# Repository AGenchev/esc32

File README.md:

# code taken from esc32, reworked to compile with GCC/freeware toolchain

I modified this and reformed the project... The goal - to compile with FOSS tools completely and to contain all source.
I put in a PCB hardware design to test it.
I probably have introduced new bugs.

First "problem": When I compiled with GCC, I got less CPU free time than the binary from esc32. Thus the control loop was closer to take 100% of the CPU time.
I considered this dangerous, because the control loop is timer-driven, e.t. in IRQ. Resolution path taken: to rewrite the control loop in integer. Most of it's done, RPM calculation is still in floating point though.

The ESC code is in <a href=https://github.com/AGenchev/esc32/tree/gelemod02/onboard>"onboard"</a> directory. <br/>
The <a href=https://github.com/AGenchev/esc32/tree/gelemod02/ground>"ground"</a> directory contains the utility which tunes the rpm PID and the current limiter PID. It does not work yet with my hardware as I have not modified it. Actually I use the ESC with current limiter turned off.

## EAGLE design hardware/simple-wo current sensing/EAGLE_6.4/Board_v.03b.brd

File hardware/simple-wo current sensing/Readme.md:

This was designed for a friend who wanted simplest design. Current sensing amplifier and shunt were removed.

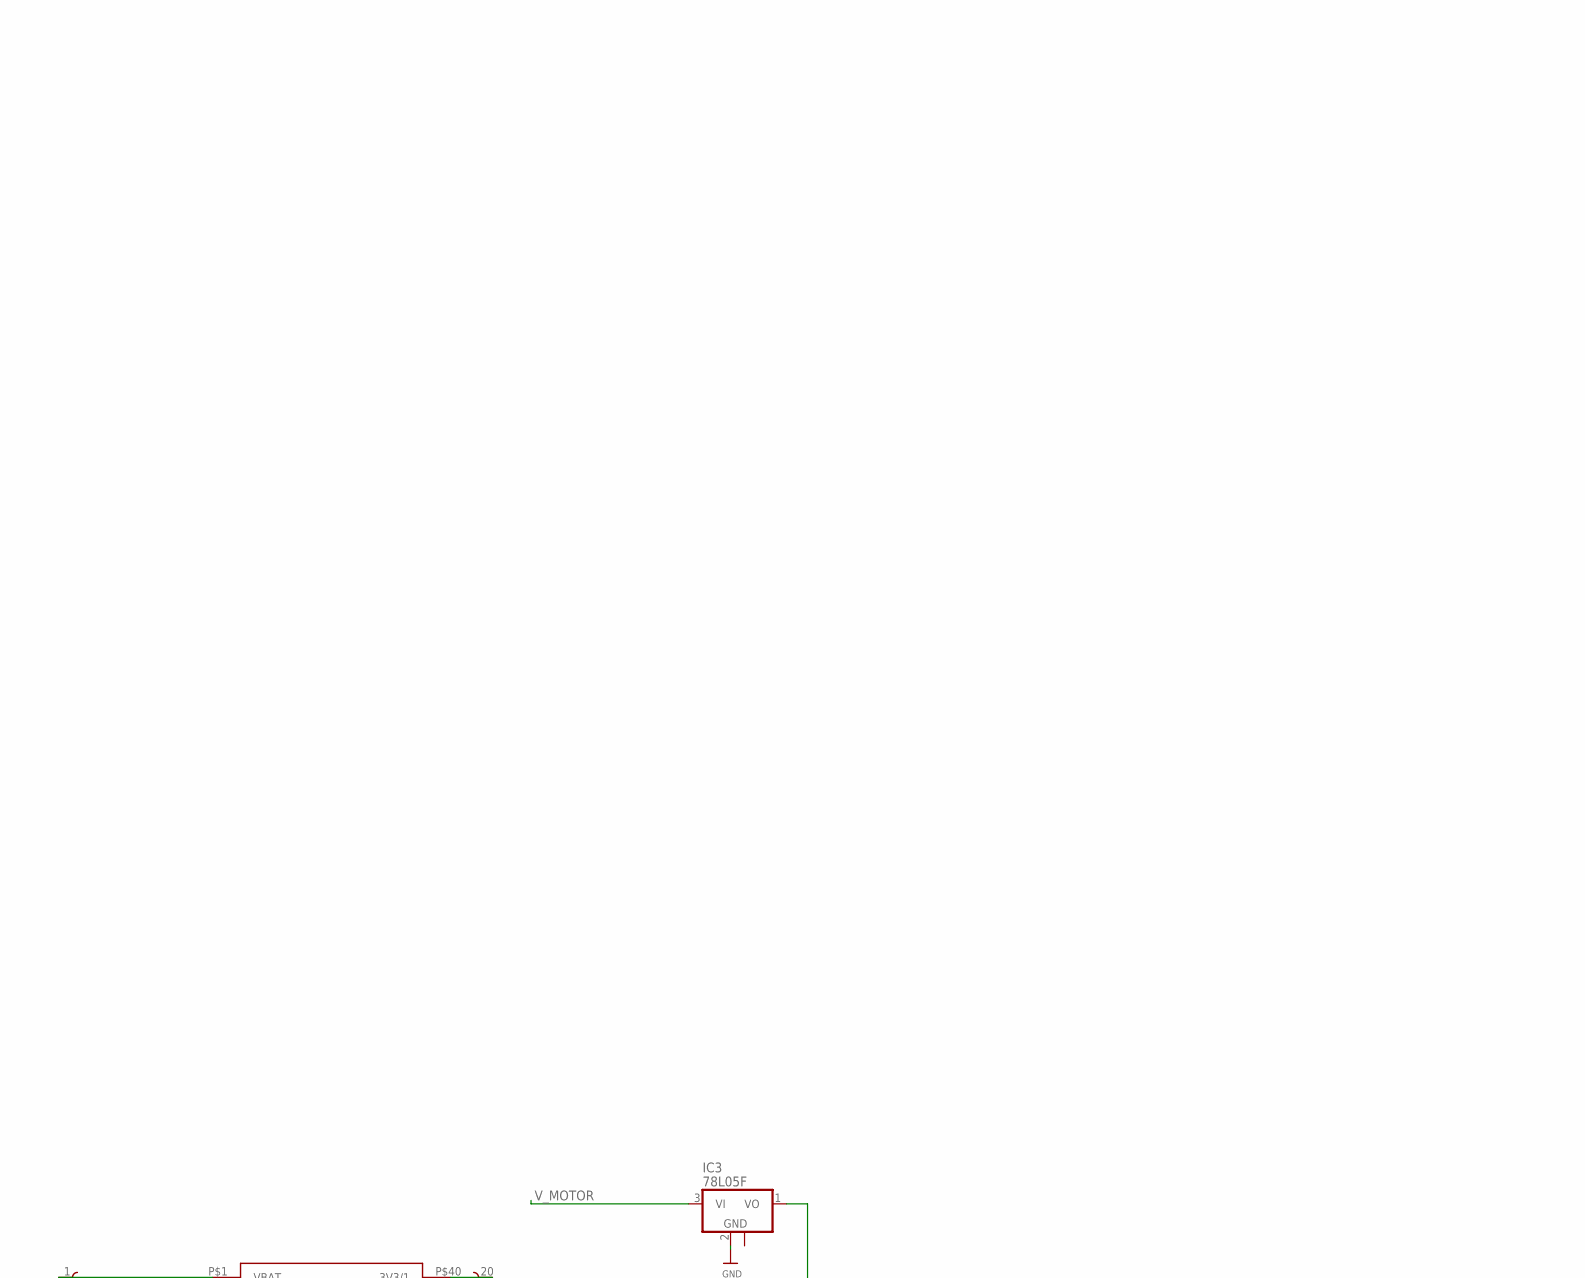
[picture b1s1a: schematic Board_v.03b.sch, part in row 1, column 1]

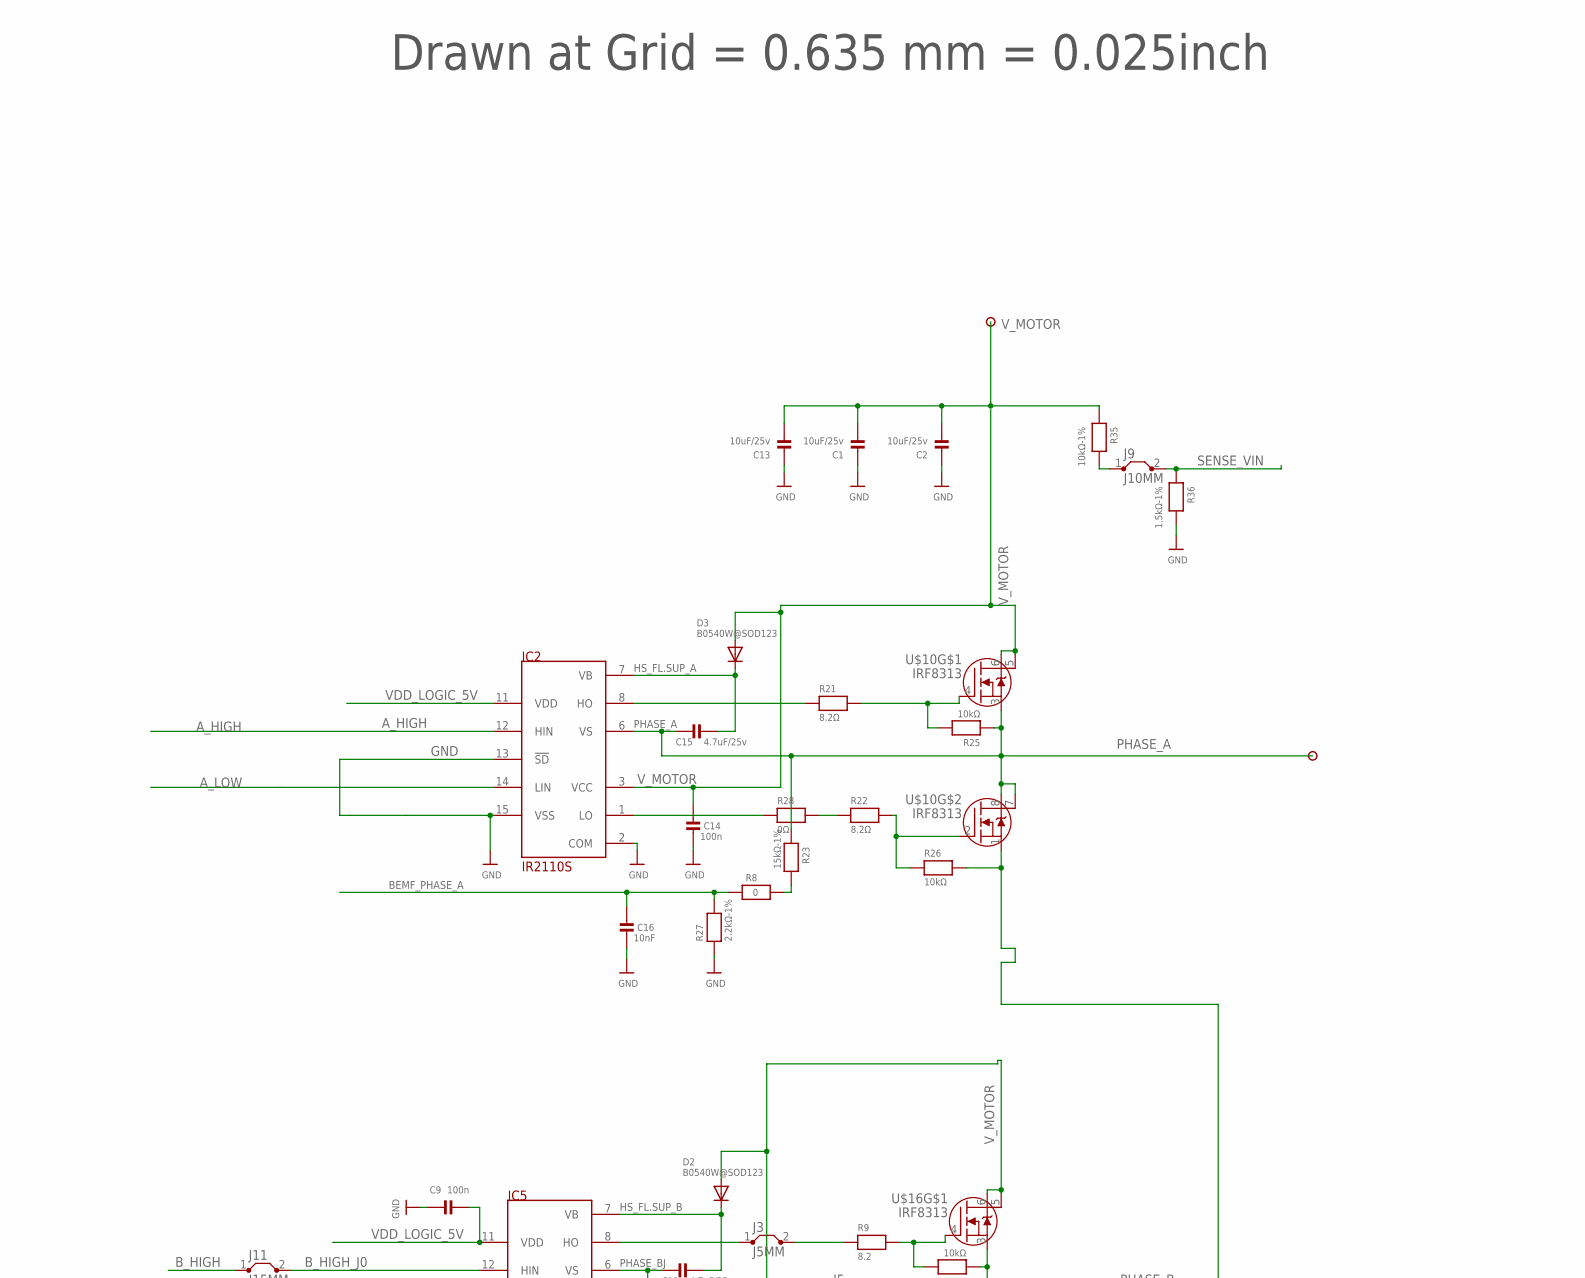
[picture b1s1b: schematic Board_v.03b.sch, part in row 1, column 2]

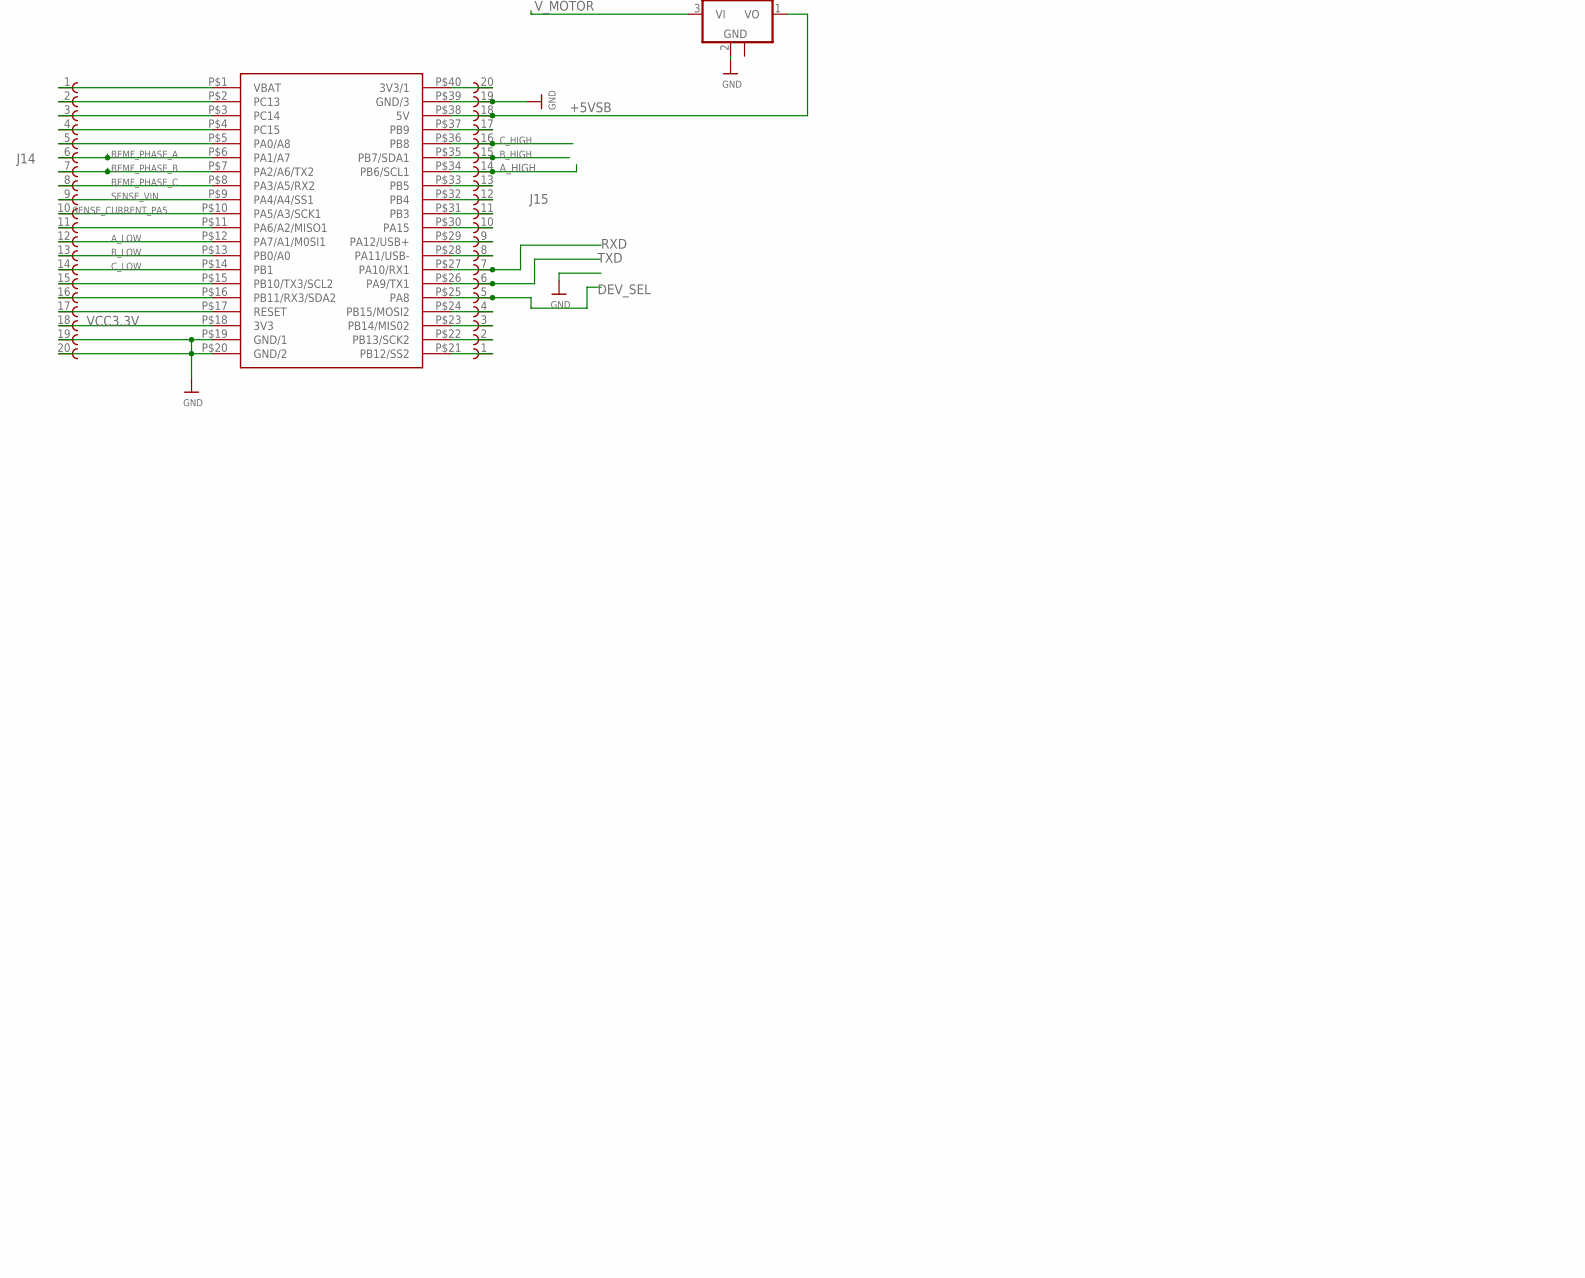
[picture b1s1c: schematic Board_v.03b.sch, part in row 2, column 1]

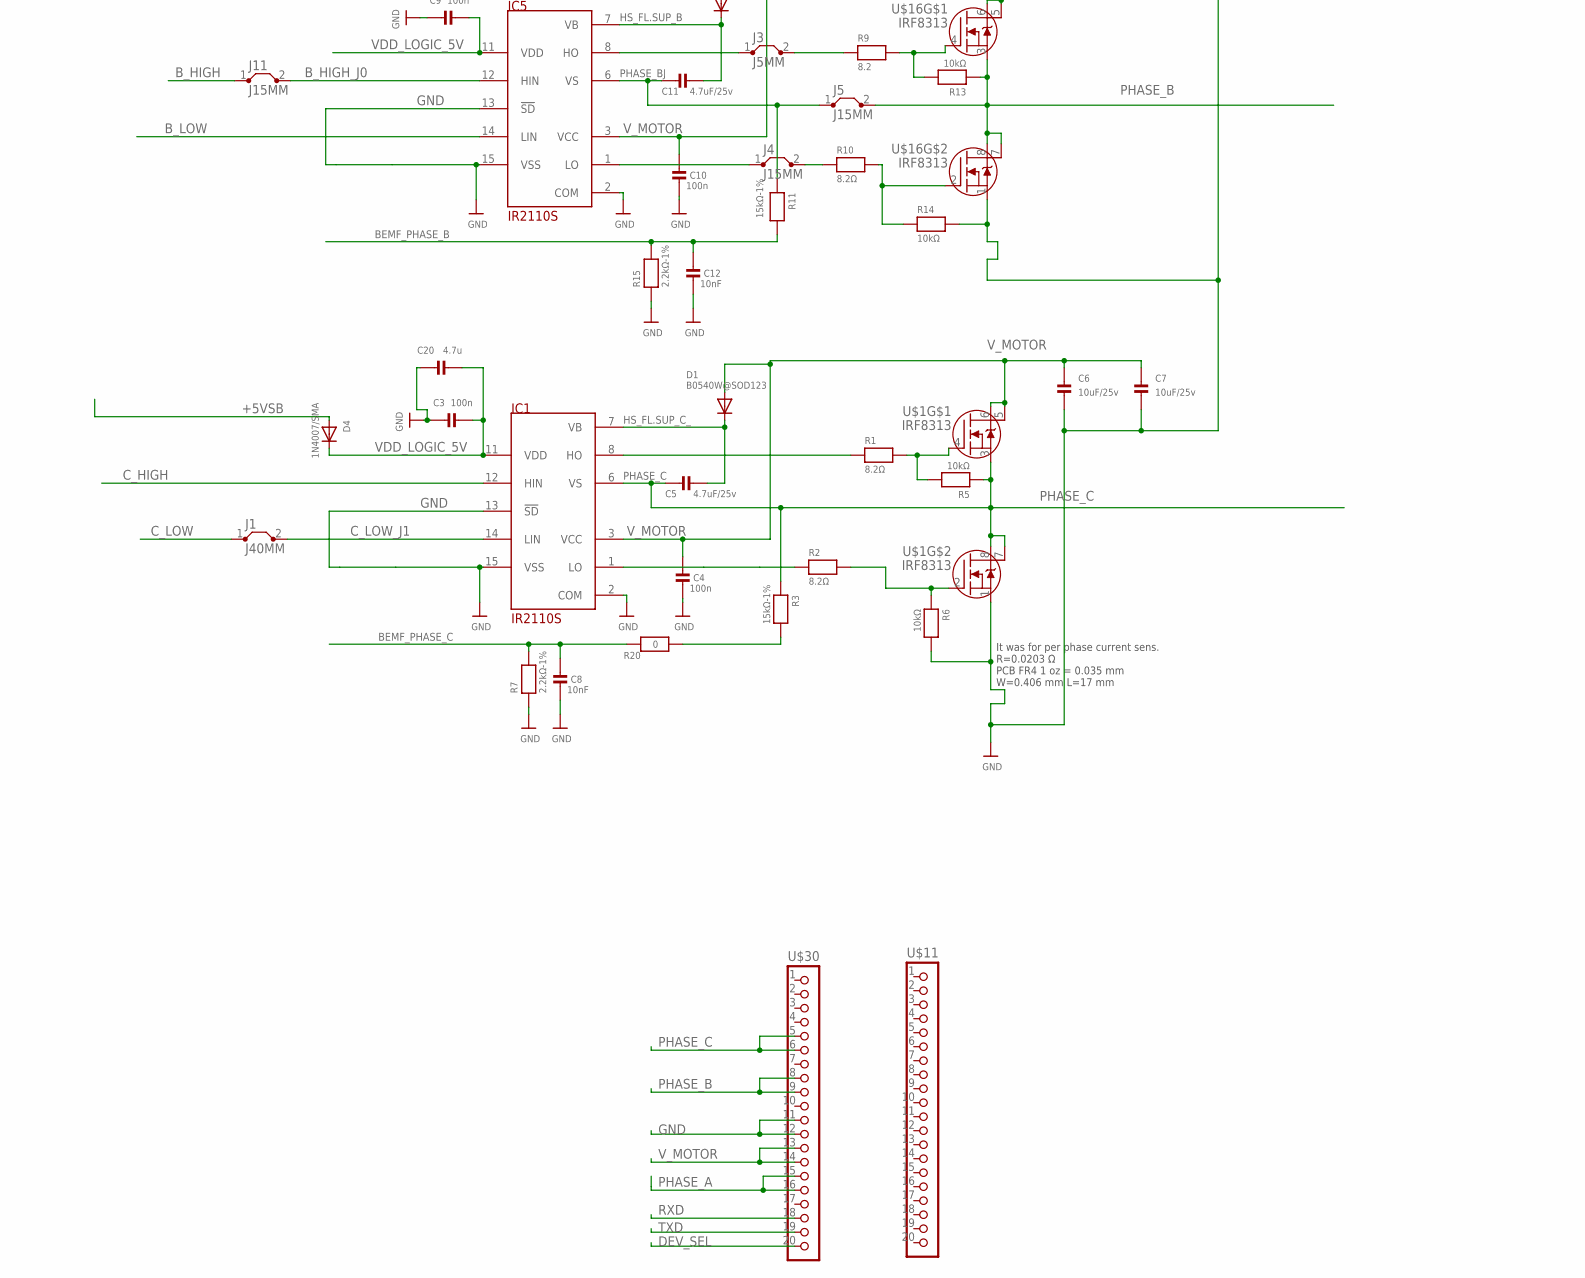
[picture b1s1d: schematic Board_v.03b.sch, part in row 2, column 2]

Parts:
C1, C2, C6, C7, C13: 10uF/25v; _0805MP
C3: 100n; _0805MP
C4, C9, C10, C14: 100n; _0603MP
C5, C11, C15: 4.7uF/25v; _0805MP
C8, C12, C16: 10nF; _0805MP
C20: 4.7u; _0805MP
D1, D2, D3: B0540W@SOD123; SOD-123
D4: 1N4007/SMA; SMADIODE
IC1, IC2, IC5: IR2110S; SO-16DW
IC3: 78L05F; SOT89
J1: J40MM
J3: J5MM; 05
J4, J5, J11: J15MM; 15
J9: J10MM; 10
J14, J15: 61002013321; CON-20PIN-SMD-MANUALLY-BENT-FROM-NON-SMD
PHASE_C: PHASE_C; PAD
R1, R2, R10, R21, R22: 8.2Ω; _0805MP
R3, R11, R23: 15kΩ-1%; _0805MP
R5, R6, R13, R14, R25, R26: 10kΩ; _0805MP
R7, R15, R27: 2.2kΩ-1%; _0805MP
R8, R20: 0; _0805MP
R9: 8.2; _0805MP
R28: 0Ω; _0805MP
R35: 10kΩ-1%; _0805MP
R36: 1.5kΩ-1%; _0805MP
U$1, U$10, U$16: IRF8313; SO08
U$11, U$30: CON_HEADER_1X20; M1X20_SMD_2.54MM/0.1"_LONGTRACKS
U$36: BLUEPILL; 40-DIP-BLUE-PIL
V_MOTOR: V_MOTOR; PAD

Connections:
+5VSB: D4.A, IC3.1 (VO), J15.18, U$36.P$38 (5V)
A_HIGH: IC2.12 (HIN), J15.14, U$36.P$34 (PB6/SCL1)
A_LOW: IC2.14 (LIN), J14.12, U$36.P$12 (PA7/A1/M0SI1)
BEMF_PHASE_A: C16.2, J14.6, R8.1, R27.2, U$36.P$6 (PA1/A7)
BEMF_PHASE_B: C12.2, J14.7, R11.2, R15.2, U$36.P$7 (PA2/A6/TX2)
BEMF_PHASE_C: C8.2, J14.8, R7.2, R20.2, U$36.P$8 (PA3/A5/RX2)
B_HIGH: J11.1, J15.15, U$36.P$35 (PB7/SDA1)
B_HIGH_J0: IC5.12 (HIN), J11.2
B_LOW: IC5.14 (LIN), J14.13, U$36.P$13 (PB0/A0)
C_HIGH: IC1.12 (HIN), J15.16, U$36.P$36 (PB8)
C_LOW: J1.1, J14.14, U$36.P$14 (PB1)
C_LOW_J1: IC1.14 (LIN), J1.2
DEV_SEL: J15.5, U$30.20, U$36.P$25 (PA8)
GND: C1.1, C2.1, C3.1, C4.1, C6.2, C7.2, C8.1, C9.1, C10.1, C12.1, C13.1, C14.1, C16.1, C20.1, IC1.2 (COM), IC1.13 (!SD), IC1.15 (VSS), IC2.2 (COM), IC2.13 (!SD), IC2.15 (VSS), IC3.2 (GND), IC5.2 (COM), IC5.13 (!SD), IC5.15 (VSS), J14.19, J14.20, J15.19, R6.2, R7.1, R14.2, R15.1, R26.2, R27.1, R36.2, U$1.1 (S), U$10.1 (S), U$16.1 (S), U$30.11, U$30.12, U$36.P$19 (GND/1), U$36.P$20 (GND/2), U$36.P$39 (GND/3)
HS_FL.SUP_A: C15.1, D3.C, IC2.7 (VB)
HS_FL.SUP_B: C11.1, D2.C, IC5.7 (VB)
HS_FL.SUP_C_: C5.1, D1.C, IC1.7 (VB)
unnamed: R1.2, R5.2, U$1.4 (G)
unnamed: J3.2, R9.1
unnamed: R2.2, R6.1, U$1.2 (G)
unnamed: IC1.8 (HO), R1.1
unnamed: IC1.1 (LO), R2.1
unnamed: R8.2, R23.2
unnamed: R3.2, R20.1
unnamed: R9.2, R13.2, U$16.4 (G)
unnamed: IC5.8 (HO), J3.1
unnamed: R10.2, R14.1, U$16.2 (G)
unnamed: J4.2, R10.1
unnamed: IC5.1 (LO), J4.1
unnamed: R21.2, R25.2, U$10.4 (G)
unnamed: R22.2, R26.1, U$10.2 (G)
unnamed: IC2.8 (HO), R21.1
unnamed: R22.1, R28.2
unnamed: IC2.1 (LO), R28.1
unnamed: J14.5, U$36.P$5 (PA0/A8)
unnamed: J9.1, R35.2
unnamed: J14.1, U$36.P$1 (VBAT)
unnamed: J14.2, U$36.P$2 (PC13)
unnamed: J14.3, U$36.P$3 (PC14)
unnamed: J14.4, U$36.P$4 (PC15)
unnamed: J14.11, U$36.P$11 (PA6/A2/MISO1)
unnamed: J14.15, U$36.P$15 (PB10/TX3/SCL2)
unnamed: J14.16, U$36.P$16 (PB11/RX3/SDA2)
unnamed: J14.17, U$36.P$17 (RESET)
unnamed: J15.1, U$36.P$21 (PB12/SS2)
unnamed: J15.2, U$36.P$22 (PB13/SCK2)
unnamed: J15.3, U$36.P$23 (PB14/MIS02)
unnamed: J15.4, U$36.P$24 (PB15/MOSI2)
unnamed: J15.8, U$36.P$28 (PA11/USB-)
unnamed: J15.9, U$36.P$29 (PA12/USB+)
unnamed: J15.10, U$36.P$30 (PA15)
unnamed: J15.11, U$36.P$31 (PB3)
unnamed: J15.12, U$36.P$32 (PB4)
unnamed: J15.13, U$36.P$33 (PB5)
unnamed: J15.17, U$36.P$37 (PB9)
unnamed: J15.20, U$36.P$40 (3V3/1)
PHASE_A: C15.2, IC2.6 (VS), PHASE_C.1, R23.1, R25.1, U$10.3 (S), U$10.7 (D), U$10.8 (D), U$30.15, U$30.16
PHASE_B: J5.2, R13.1, U$16.3 (S), U$16.7 (D), U$16.8 (D), U$30.8, U$30.9
PHASE_BJ: C11.2, IC5.6 (VS), J5.1, R11.1
PHASE_C: C5.2, IC1.6 (VS), R3.1, R5.1, U$1.3 (S), U$1.7 (D), U$1.8 (D), U$30.5, U$30.6
RXD: J15.7, U$30.18, U$36.P$27 (PA10/RX1)
SENSE_CURRENT_PA5: J14.10, U$36.P$10 (PA5/A3/SCK1)
SENSE_VIN: J9.2, J14.9, R36.1, U$36.P$9 (PA4/A4/SS1)
TXD: J15.6, U$30.19, U$36.P$26 (PA9/TX1)
VCC3.3V: J14.18, U$36.P$18 (3V3)
VDD_LOGIC_5V: C3.2, C9.2, C20.2, D4.C, IC1.11 (VDD), IC2.11 (VDD), IC5.11 (VDD)
V_MOTOR: C1.2, C2.2, C4.2, C6.1, C7.1, C10.2, C13.2, C14.2, D1.A, D2.A, D3.A, IC1.3 (VCC), IC2.3 (VCC), IC3.3 (VI), IC5.3 (VCC), R35.1, U$1.5 (D), U$1.6 (D), U$10.5 (D), U$10.6 (D), U$16.5 (D), U$16.6 (D), U$30.13, U$30.14, V_MOTOR.1

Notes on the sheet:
Drawn at Grid = 0.635 mm = 0.025inch
It was for per phase current sens. R=0.0203 Ω PCB FR4 1 oz = 0.035 mm W=0.406 mm L=17 mm

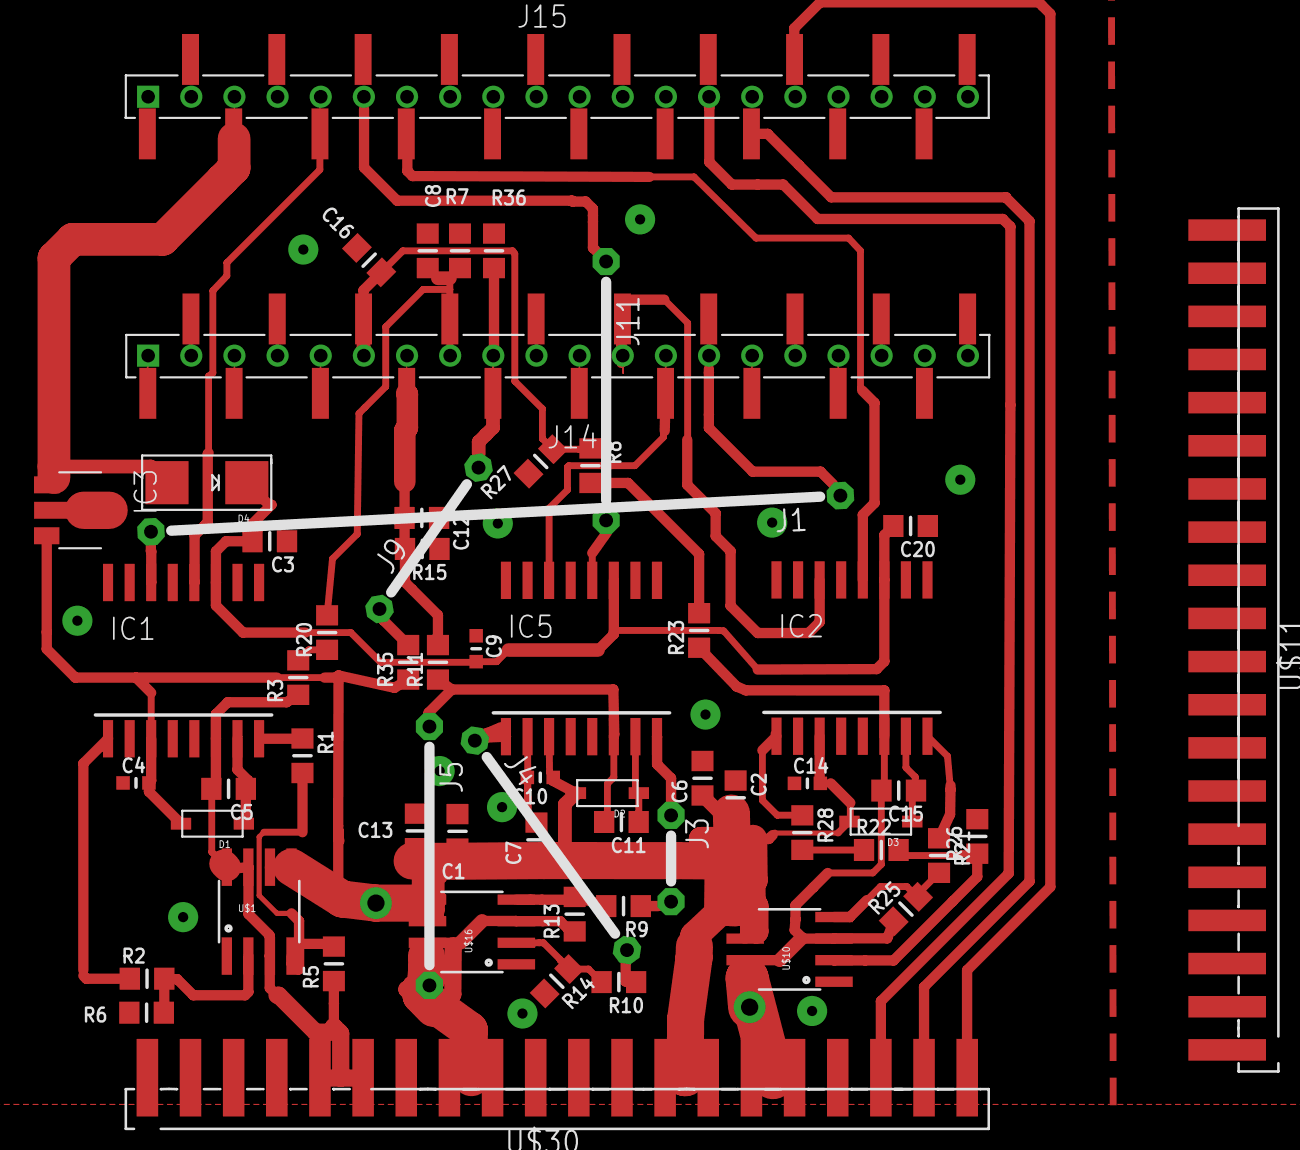
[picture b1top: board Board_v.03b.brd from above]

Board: 2 copper layers, 66 parts (0 on the bottom side), 67 nets.

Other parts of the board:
U$13, U$21: MOUNTINGHOLE_2.8

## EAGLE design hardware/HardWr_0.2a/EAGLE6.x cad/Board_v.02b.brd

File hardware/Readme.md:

The hardware was converted from EAGLE to KiCad<br/>
<b>Note:</b> I will post hardware which is not fully compatible with the official code of ESC32.
versions:<br/><br/>
a href=https://github.com/AGenchev/esc32/tree/gelemod02/hardware/HardWr_0.2a>HardWr_0.2</a> is on single-layer (w. bridges) routed PCB. ESC32 works on bluepill.
The CPU is STM32F103C8T6, found on cheap chinese boards called Bluepill.
Uses IR2110S NMOSFET gate drivers.
<br /><b>WARNING:</b> The Vcc of the motor and of the IR2110S is tied together so the Vcc shall not exceed 20V for this project.
<br />Note: My test PCB is not intended to fly or to drive racing car. I just wanted to drive a BLDC motor with fixed RPM indoor. 
<br />Control: over serial interface. I set baudrate to 230400, 8-N-1. PA8 is used as "Device Select", active=1 to enable the serial interface on PA9 & PA10. There are CLI interface and binary interface.
Other interfaces which were supported by ESC32 (CAN bus, OneWire, PWM) are there, but are disabled via #UNDEF directive in config.h. because I don't need 'em.

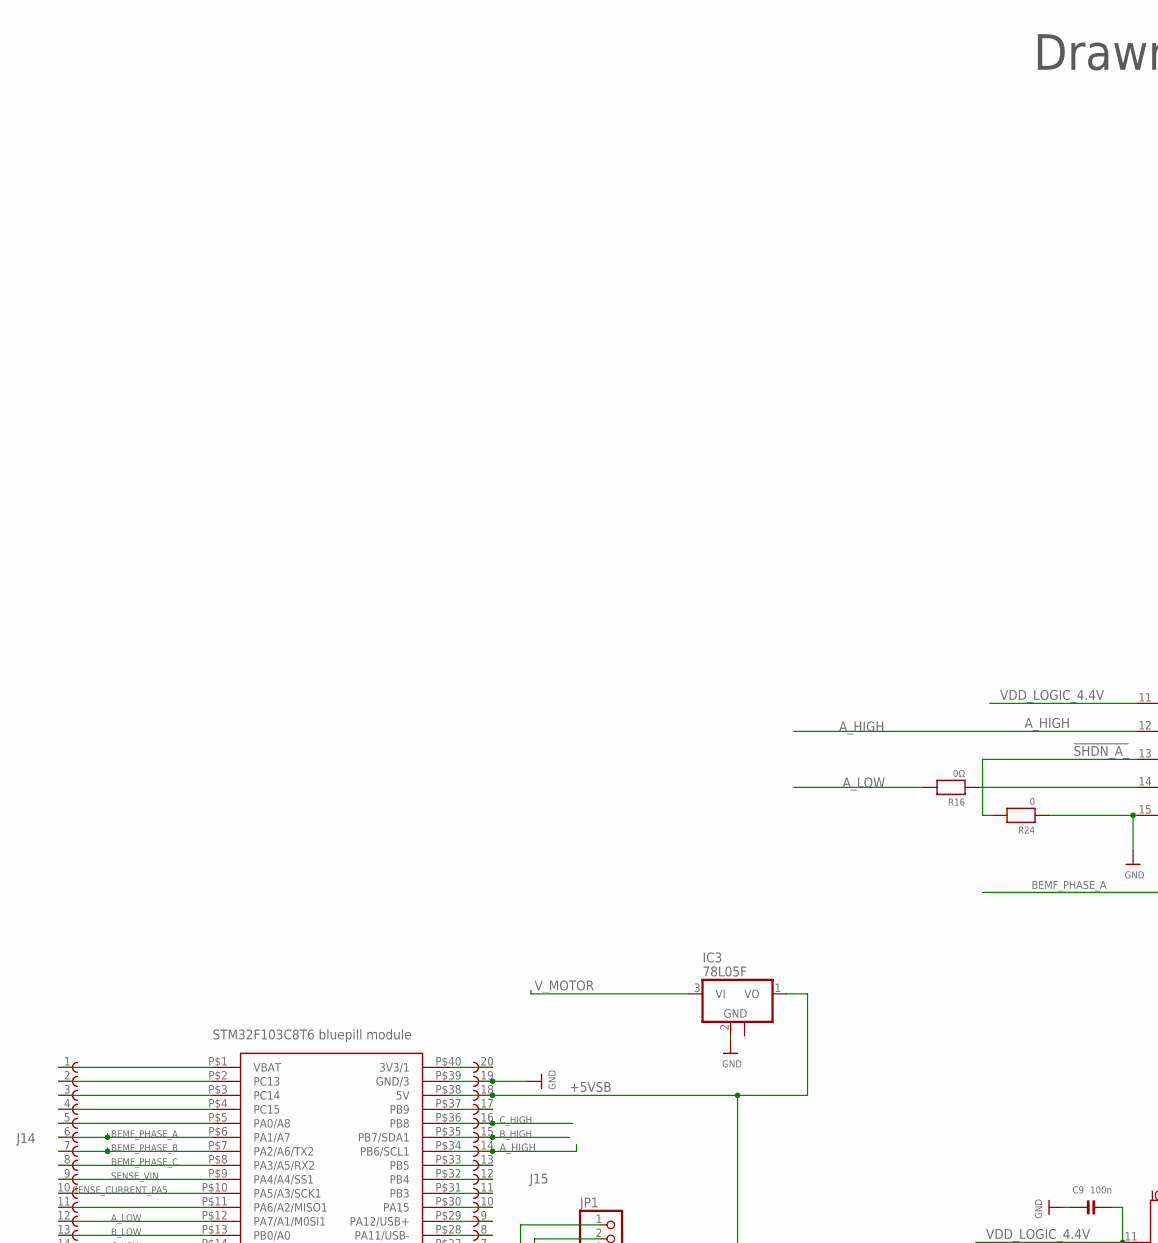
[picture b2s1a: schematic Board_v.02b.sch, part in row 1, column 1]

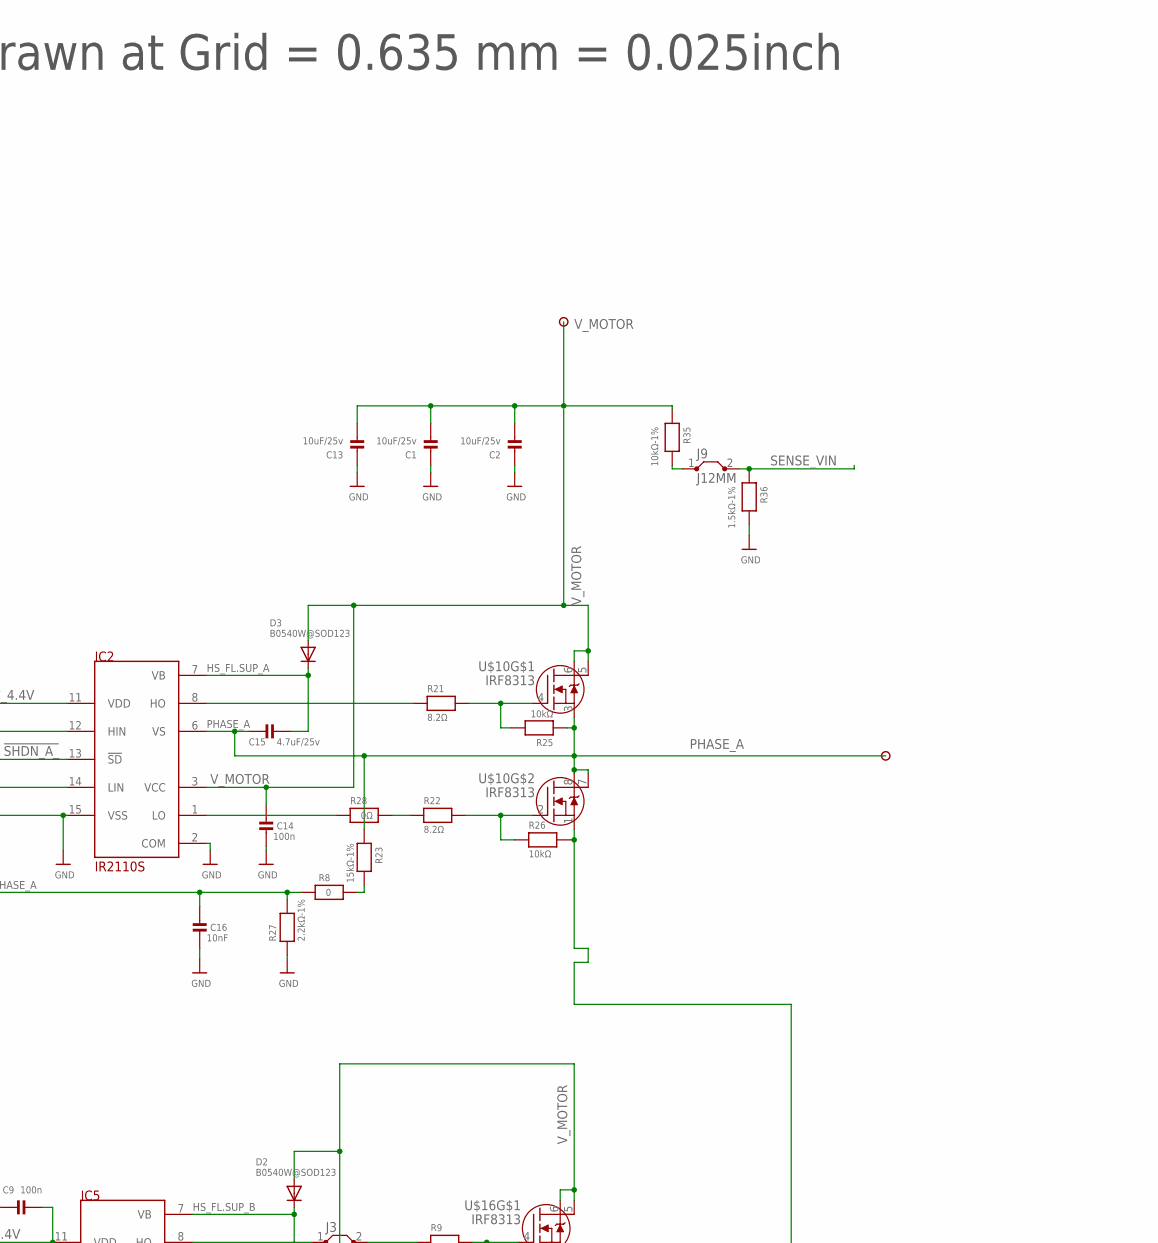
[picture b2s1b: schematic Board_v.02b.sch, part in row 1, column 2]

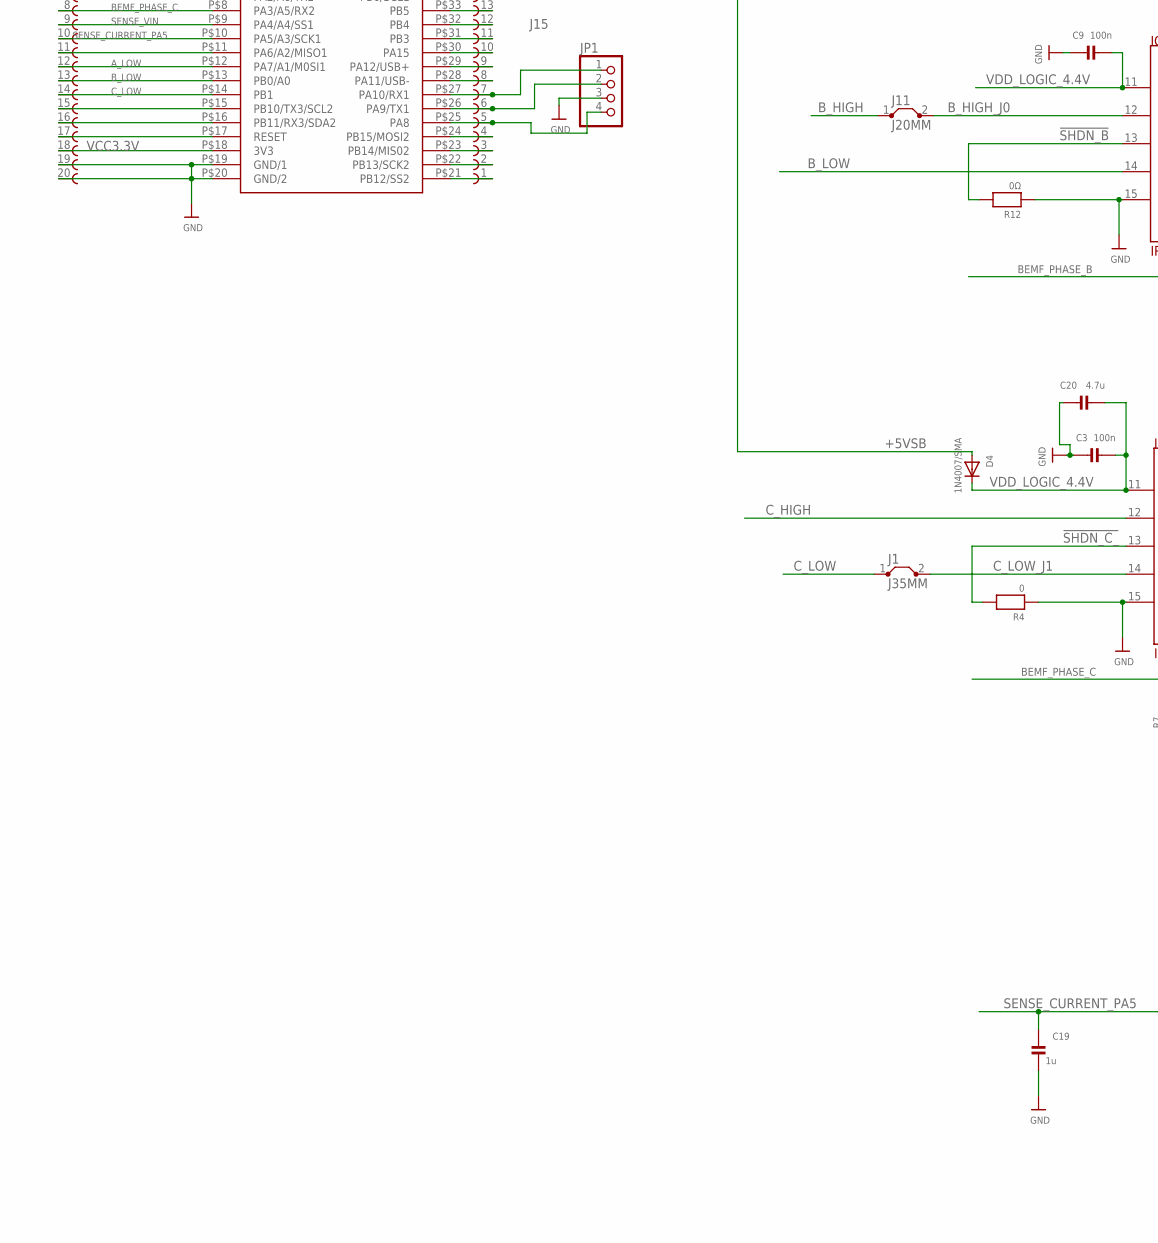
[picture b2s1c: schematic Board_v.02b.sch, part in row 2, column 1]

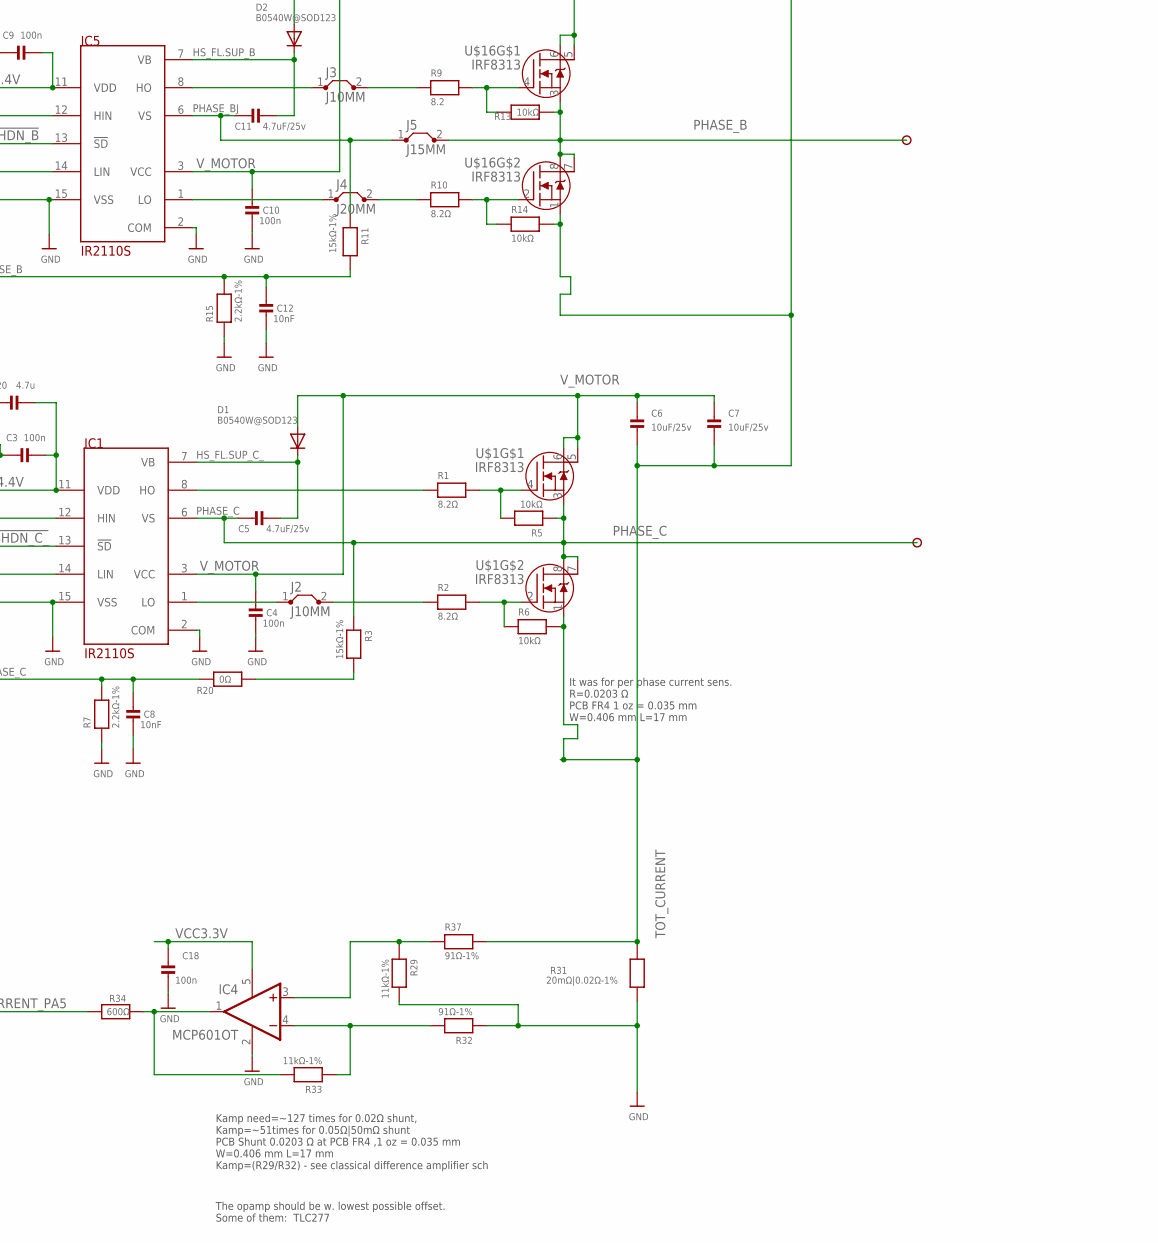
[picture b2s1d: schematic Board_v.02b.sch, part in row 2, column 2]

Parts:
BLUEPILL-STM32F103C8T6_MODULE: BLUEPILL; 40-DIP-BLUE-PIL
C1, C2, C6, C7, C13: 10uF/25v; _0805MP
C3, C18: 100n; _0805MP
C4, C9, C10, C14: 100n; _0603MP
C5, C11, C15: 4.7uF/25v; _0805MP
C8, C12, C16: 10nF; _0805MP
C19: 1u; _0805MP
C20: 4.7u; _0805MP
D1, D2, D3: B0540W@SOD123; SOD-123
D4: 1N4007/SMA; SMADIODE
IC1, IC2, IC5: IR2110S; SO-16DW
IC3: 78L05F; SOT89
IC4: MCP601OT; SOT23-5
J1: J35MM
J2, J3: J10MM; 10
J4, J11: J20MM; 20
J5: J15MM; 15
J9: J12MM; 12
J14, J15: 61002013321; CON-20PIN-SMD-MANUALLY-BENT-FROM-NON-SMD
JP1: PINHD-1X04_2.54-SMD; 1X04SMD
PHASE_A: PHASE_A; PAD
PHASE_B: PHASE_B; PAD
PHASE_C: PHASE_C; PAD
R1, R2, R10, R21, R22: 8.2Ω; _0805MP
R3, R11, R23: 15kΩ-1%; _0805MP
R4, R8, R24: 0; _0805MP
R5, R6, R13, R14, R25, R26: 10kΩ; _0805MP
R7, R15, R27: 2.2kΩ-1%; _0805MP
R9: 8.2; _0805MP
R12, R16, R20, R28: 0Ω; _0805MP
R29, R33: 11kΩ-1%; _0805MP
R31: 20mΩ|0.02Ω-1%; 2512
R32, R37: 91Ω-1%; _0805MP
R34: 600Ω; _0805MP
R35: 10kΩ-1%; _0805MP
R36: 1.5kΩ-1%; _0805MP
U$1, U$10, U$16: IRF8313; SO08
V_MOTOR: V_MOTOR; PAD

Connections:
!SHDN_A_: IC2.13 (!SD), R24.2
!SHDN_B: IC5.13 (!SD), R12.2
!SHDN_C_: IC1.13 (!SD), R4.2
+5VSB: BLUEPILL-STM32F103C8T6_MODULE.P$38 (5V), D4.A, IC3.1 (VO), J15.18
A_HIGH: BLUEPILL-STM32F103C8T6_MODULE.P$34 (PB6/SCL1), IC2.12 (HIN), J15.14
A_LOW: BLUEPILL-STM32F103C8T6_MODULE.P$12 (PA7/A1/M0SI1), J14.12, R16.2
BEMF_PHASE_A: BLUEPILL-STM32F103C8T6_MODULE.P$6 (PA1/A7), C16.2, J14.6, R8.1, R27.2
BEMF_PHASE_B: BLUEPILL-STM32F103C8T6_MODULE.P$7 (PA2/A6/TX2), C12.2, J14.7, R11.2, R15.2
BEMF_PHASE_C: BLUEPILL-STM32F103C8T6_MODULE.P$8 (PA3/A5/RX2), C8.2, J14.8, R7.2, R20.2
B_HIGH: BLUEPILL-STM32F103C8T6_MODULE.P$35 (PB7/SDA1), J11.1, J15.15
B_HIGH_J0: IC5.12 (HIN), J11.2
B_LOW: BLUEPILL-STM32F103C8T6_MODULE.P$13 (PB0/A0), IC5.14 (LIN), J14.13
C_HIGH: BLUEPILL-STM32F103C8T6_MODULE.P$36 (PB8), IC1.12 (HIN), J15.16
C_LOW: BLUEPILL-STM32F103C8T6_MODULE.P$14 (PB1), J1.1, J14.14
C_LOW_J1: IC1.14 (LIN), J1.2
GND: BLUEPILL-STM32F103C8T6_MODULE.P$19 (GND/1), BLUEPILL-STM32F103C8T6_MODULE.P$20 (GND/2), BLUEPILL-STM32F103C8T6_MODULE.P$39 (GND/3), C1.1, C2.1, C3.1, C4.1, C8.1, C9.1, C10.1, C12.1, C13.1, C14.1, C16.1, C18.1, C19.1, C20.1, IC1.2 (COM), IC1.15 (VSS), IC2.2 (COM), IC2.15 (VSS), IC3.2 (GND), IC4.2 (V-), IC5.2 (COM), IC5.15 (VSS), J14.19, J14.20, J15.19, JP1.3, R4.1, R7.1, R12.1, R15.1, R24.1, R27.1, R29.2, R31.2, R32.1, R36.2
HS_FL.SUP_A: C15.1, D3.C, IC2.7 (VB)
HS_FL.SUP_B: C11.1, D2.C, IC5.7 (VB)
HS_FL.SUP_C_: C5.1, D1.C, IC1.7 (VB)
unnamed: R1.2, R5.2, U$1.4 (G)
unnamed: J3.2, R9.1
unnamed: R2.2, R6.1, U$1.2 (G)
unnamed: IC1.8 (HO), R1.1
unnamed: J2.2, R2.1
unnamed: IC1.1 (LO), J2.1
unnamed: R8.2, R23.2
unnamed: R3.2, R20.1
unnamed: R9.2, R13.2, U$16.4 (G)
unnamed: IC5.8 (HO), J3.1
unnamed: R10.2, R14.1, U$16.2 (G)
unnamed: J4.2, R10.1
unnamed: IC5.1 (LO), J4.1
unnamed: IC4.4 (-IN), R32.2, R33.1
unnamed: R21.2, R25.2, U$10.4 (G)
unnamed: R22.2, R26.1, U$10.2 (G)
unnamed: IC2.8 (HO), R21.1
unnamed: R22.1, R28.2
unnamed: IC2.1 (LO), R28.1
unnamed: IC4.1 (OUT), R33.2, R34.1
unnamed: BLUEPILL-STM32F103C8T6_MODULE.P$5 (PA0/A8), J14.5
unnamed: IC2.14 (LIN), R16.1
unnamed: J9.1, R35.2
unnamed: BLUEPILL-STM32F103C8T6_MODULE.P$26 (PA9/TX1), J15.6, JP1.2
unnamed: BLUEPILL-STM32F103C8T6_MODULE.P$27 (PA10/RX1), J15.7, JP1.1
unnamed: IC4.3 (+IN), R29.1, R37.1
unnamed: BLUEPILL-STM32F103C8T6_MODULE.P$1 (VBAT), J14.1
unnamed: BLUEPILL-STM32F103C8T6_MODULE.P$2 (PC13), J14.2
unnamed: BLUEPILL-STM32F103C8T6_MODULE.P$3 (PC14), J14.3
unnamed: BLUEPILL-STM32F103C8T6_MODULE.P$4 (PC15), J14.4
unnamed: BLUEPILL-STM32F103C8T6_MODULE.P$11 (PA6/A2/MISO1), J14.11
unnamed: BLUEPILL-STM32F103C8T6_MODULE.P$15 (PB10/TX3/SCL2), J14.15
unnamed: BLUEPILL-STM32F103C8T6_MODULE.P$16 (PB11/RX3/SDA2), J14.16
unnamed: BLUEPILL-STM32F103C8T6_MODULE.P$17 (RESET), J14.17
unnamed: BLUEPILL-STM32F103C8T6_MODULE.P$21 (PB12/SS2), J15.1
unnamed: BLUEPILL-STM32F103C8T6_MODULE.P$22 (PB13/SCK2), J15.2
unnamed: BLUEPILL-STM32F103C8T6_MODULE.P$23 (PB14/MIS02), J15.3
unnamed: BLUEPILL-STM32F103C8T6_MODULE.P$24 (PB15/MOSI2), J15.4
unnamed: BLUEPILL-STM32F103C8T6_MODULE.P$25 (PA8), J15.5, JP1.4
unnamed: BLUEPILL-STM32F103C8T6_MODULE.P$28 (PA11/USB-), J15.8
unnamed: BLUEPILL-STM32F103C8T6_MODULE.P$29 (PA12/USB+), J15.9
unnamed: BLUEPILL-STM32F103C8T6_MODULE.P$30 (PA15), J15.10
unnamed: BLUEPILL-STM32F103C8T6_MODULE.P$31 (PB3), J15.11
unnamed: BLUEPILL-STM32F103C8T6_MODULE.P$32 (PB4), J15.12
unnamed: BLUEPILL-STM32F103C8T6_MODULE.P$33 (PB5), J15.13
unnamed: BLUEPILL-STM32F103C8T6_MODULE.P$37 (PB9), J15.17
unnamed: BLUEPILL-STM32F103C8T6_MODULE.P$40 (3V3/1), J15.20
PHASE_A: C15.2, IC2.6 (VS), PHASE_C.1, R23.1, R25.1, U$10.3 (S), U$10.7 (D), U$10.8 (D)
PHASE_B: J5.2, PHASE_B.1, R13.1, U$16.3 (S), U$16.7 (D), U$16.8 (D)
PHASE_BJ: C11.2, IC5.6 (VS), J5.1, R11.1
PHASE_C: C5.2, IC1.6 (VS), PHASE_A.1, R3.1, R5.1, U$1.3 (S), U$1.7 (D), U$1.8 (D)
SENSE_CURRENT_PA5: BLUEPILL-STM32F103C8T6_MODULE.P$10 (PA5/A3/SCK1), C19.2, J14.10, R34.2
SENSE_VIN: BLUEPILL-STM32F103C8T6_MODULE.P$9 (PA4/A4/SS1), J9.2, J14.9, R36.1
TOT_CURRENT: C6.2, C7.2, R6.2, R14.2, R26.2, R31.1, R37.2, U$1.1 (S), U$10.1 (S), U$16.1 (S)
VCC3.3V: BLUEPILL-STM32F103C8T6_MODULE.P$18 (3V3), C18.2, IC4.5 (V+), J14.18
VDD_LOGIC_4.4V: C3.2, C9.2, C20.2, D4.C, IC1.11 (VDD), IC2.11 (VDD), IC5.11 (VDD)
V_MOTOR: C1.2, C2.2, C4.2, C6.1, C7.1, C10.2, C13.2, C14.2, D1.A, D2.A, D3.A, IC1.3 (VCC), IC2.3 (VCC), IC3.3 (VI), IC5.3 (VCC), R35.1, U$1.5 (D), U$1.6 (D), U$10.5 (D), U$10.6 (D), U$16.5 (D), U$16.6 (D), V_MOTOR.1

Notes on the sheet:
Drawn at Grid = 0.635 mm = 0.025inch
It was for per phase current sens. R=0.0203 Ω PCB FR4 1 oz = 0.035 mm W=0.406 mm L=17 mm
Kamp need=~127 times for 0.02Ω shunt, Kamp=~51times for 0.05Ω|50mΩ shunt PCB Shunt 0.0203 Ω at PCB FR4 ,1 oz = 0.035 mm W=0.406 mm L=17 mm Kamp=(R29/R32) - see classical difference amplifier sch
The opamp should be w. lowest possible offset. Some of them: TLC277

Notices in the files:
parts and their libraries:
microbuilder: This work is placed in the public domain, and may be freely used for commercial and non-commercial work with the following conditions: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
